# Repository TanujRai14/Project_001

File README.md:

# 🔌 Project_001: Smart USB Power Meter using ESP32, INA219 & OLED

This project is a compact **Smart USB Power Meter** designed using an **ESP32**, **INA219 current sensor**, and **OLED display**, all integrated on a custom **2-layer PCB**. The circuit allows real-time monitoring of **USB voltage and current** through a **Type-C connector**, displaying the results on a 0.96” OLED screen.

---

## ✨ Features

- ✅ Measures **voltage and current** of any USB-powered device
- 📟 Displays data on a **128x64 OLED** screen via **I2C**
- 📶 Powered by **ESP32** for wireless capabilities & efficient control
- 🔍 Uses **INA219** precision current sensor for accurate readings
- 🔧 Onboard **AMS1117** 5V to 3.3V regulator for safe ESP32 operation
- 🧵 Designed with **standard trace widths** (0.2mm, 0.3mm, 0.5mm)
- 🛠️ Full **GND pour** on bottom layer, all signals routed on top
- 📡 Dedicated **Antenna Keep-Out Zone** for WiFi stability

---

## 🧩 Hardware Components

| Component        | Description                                           |
|------------------|-------------------------------------------------------|
| **ESP32 Module** | WiFi-enabled microcontroller (ESP-WROOM-32)           |
| **INA219**       | I2C-based voltage and current sensor                  |
| **OLED Display** | 128x64 OLED via I2C (address: 0x3C or 0x78)           |
| **AMS1117-3.3V** | LDO regulator to step down 5V to 3.3V                  |
| **USB Type-C**   | Input connector for USB voltage/current measurement   |
| **Passives**     | Capacitors & resistors for filtering & pull-ups       |

---

## 🛠️ PCB Design Highlights

- 🔲 **2-layer PCB**
  - Top Layer: Signal routing
  - Bottom Layer: Solid GND plane for noise reduction

- 🔌 **Trace Widths**
  - Signal traces: `0.2 mm`
  - Power traces: `0.3 mm`
  - INA219 high-current path: `0.5 mm`

- 📏 **Routing Guidelines**
  - Uniform SPI/I2C trace lengths
  - Minimum crosstalk and EMI
  - Proper decoupling at power pins
  - Dedicated Keep-Out Zone for ESP32 Antenna

---

## ⚙️ Working Principle

1. A USB device is connected via the **USB Type-C** input (J1).
2. The **INA219 sensor** measures the input current and voltage.
3. **ESP32** reads the data from INA219 via **I2C protocol**.
4. The ESP32 processes the values and displays them on the **OLED**.
5. **AMS1117** provides regulated **3.3V** to ESP32 and peripherals.

---

## 🧠 ESP32 Pin Mapping

| ESP32 Pin | Connected To       | Function       |
|-----------|--------------------|----------------|
| GPIO 21   | SDA (INA219, OLED) | I2C Data (SDA) |
| GPIO 22   | SCL (INA219, OLED) | I2C Clock (SCL)|
| 3.3V      | VCC (All Modules)  | Power Supply   |
| GND       | GND Plane          | Common Ground  |

---

## 🔋 Power Supply

| Source     | Purpose                         |
|------------|----------------------------------|
| **5V Input** | USB Type-C (J1)                 |
| **3.3V Reg** | AMS1117 provides 3.3V to ESP32, INA219, OLED |

---

## 🖼 PCB Layout Summary

- 🧠 ESP32 placed at center with Antenna keep-out on the left
- 🔬 INA219 close to USB input for accurate shunt readings
- 🔌 AMS1117 and capacitors placed for clean 3.3V regulation
- 📟 OLED connector on top side for vertical screen mounting
- 📐 Optimized signal routing for analog/digital separation

---

## 📦 File Contents

- 📁 `Gerber Files` – Ready for PCB manufacturing
- 📁 `Schematic PDF` – Complete circuit diagram
- 📁 `Firmware Code` – ESP32 code to:
  - Read INA219 data
  - Update OLED display in real-time

---

## 🚀 Use Cases

- USB power monitor for embedded systems
- Current profiling for smartphones or peripherals
- Educational tool for learning power electronics and PCB design

---

## 💡 Future Improvements

- Add UART header for serial debugging/monitoring
- Add USB data passthrough or toggle switch
- Enable ESP32 WiFi mode for wireless logging and dashboard
- Add Li-ion charging support to make it portable

---

## 👨‍💻 Author

Designed  by **Tanuj Rai**

Feel free to fork and modify for your use. Pull requests are welcome!

---

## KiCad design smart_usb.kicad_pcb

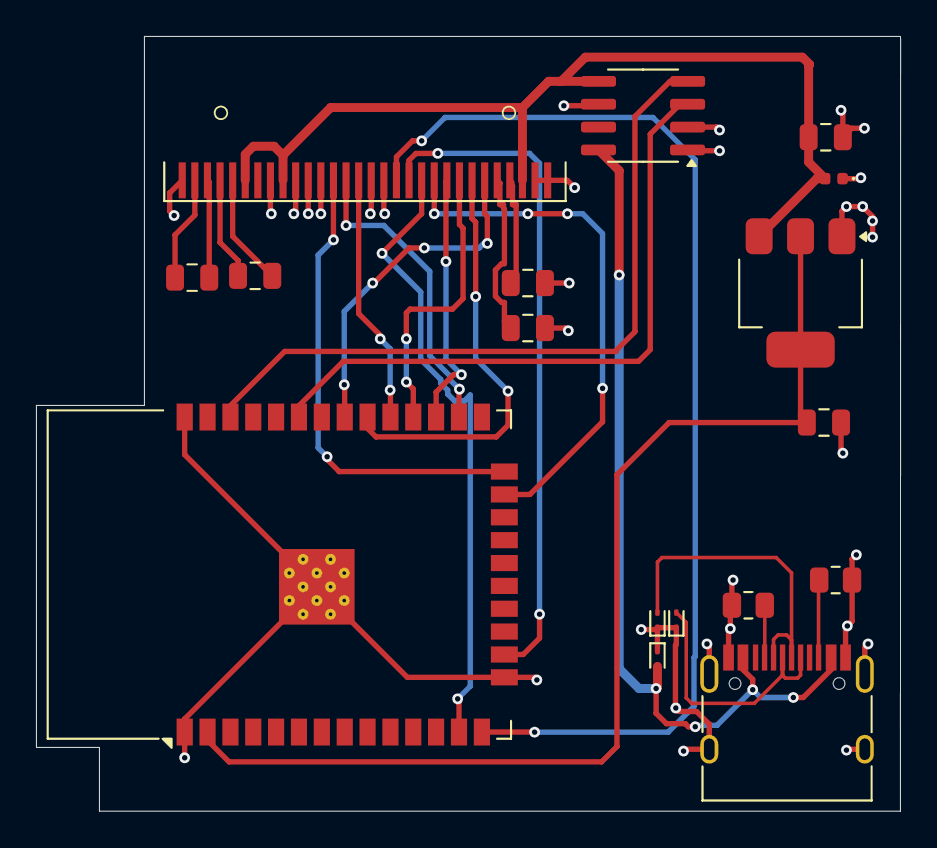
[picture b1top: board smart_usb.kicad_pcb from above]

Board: 2 copper layers, 48.0 x 43.0 mm, 17 parts (0 on the bottom side), 27 nets.

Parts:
C1: 10uF; C_0805_2012Metric
C2: 22uF; C_0805_2012Metric
C3, C4, C5: C; C_0805_2012Metric
D1: D_Schottky; D_0402_1005Metric
D2, D3, D4: ESD9B3.3ST5G; D_SOD-923
DS1: OLED-128O064D
J1: USB_C_Receptacle_USB2.0_16P; USB_C_Receptacle_HRO_TYPE-C-31-M-12
R1, R2: 5.1K; R_0805_2012Metric
R3: 910K; C_0805_2012Metric
U1: INA219AxD; SOIC-8_3.9x4.9mm_P1.27mm
U2: AMS1117; SOT-223-3_TabPin2
U3: ESP32-WROOM-32

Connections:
+3.3V: C2.1, U2.2 (VO), U3.2 (VDD)
+5V: C1.1, D1.2 (A), DS1.6 (VBAT), DS1.9 (VDD), DS1.28 (VCC), U1.5 (VS), U2.3 (VI)
GND: C1.2, C2.2, C5.2, D1.1 (K), D2.1 (A1), D3.1 (A1), D4.1 (A1), DS1.1 (GND), DS1.8 (VSS), DS1.10 (BS0), DS1.11 (BS1), DS1.12 (BS2), DS1.16 (R/~W), DS1.17 (E/~RD), DS1.29 (VLSS), DS1.30 (GND), J1.A1 (GND), J1.A12 (GND), J1.B1 (GND), J1.B12 (GND), J1.S1 (SHIELD), R1.2, R2.2, R3.2, U1.1 (A1), U1.2 (A0), U1.6 (GND), U2.1 (ADJ), U3.1 (GND), U3.15 (GND), U3.38 (GND), U3.39 (GND)
unnamed: D2.2 (A2), J1.A6 (D+), J1.B6 (D+)
unnamed: D3.2 (A2), J1.A7 (D-), J1.B7 (D-)
unnamed: C4.2, DS1.5 (C1N)
unnamed: C4.1, DS1.4 (C1P)
unnamed: C3.1, DS1.2 (C2N)
unnamed: C3.2, DS1.3 (C2P)
unnamed: DS1.18 (D0), U3.14 (IO12)
unnamed: DS1.19 (D1), U3.16 (IO13)
unnamed: DS1.20 (D2), U3.13 (IO14)
unnamed: DS1.21 (D3), U3.23 (IO15)
unnamed: DS1.22 (D4), U3.27 (IO16)
unnamed: DS1.23 (D5), U3.28 (IO17)
unnamed: DS1.24 (D6), U3.30 (IO18)
unnamed: DS1.25 (D7), U3.31 (IO19)
unnamed: DS1.15 (D/~C), U3.29 (IO5)
unnamed: DS1.26 (IREF), R3.1
unnamed: C5.1, DS1.27 (VCOMH)
unnamed: DS1.13 (~CS), U3.24 (IO2)
unnamed: DS1.14 (~RES), U3.26 (IO4)
unnamed: J1.A5 (CC1), R1.1
unnamed: J1.B5 (CC2), R2.1
SCL: U1.4 (SCL), U3.36 (IO22)
SDA: U1.3 (SDA), U3.33 (IO21)
VBUS: D4.2 (A2), J1.A4 (VBUS), J1.A9 (VBUS), J1.B4 (VBUS), J1.B9 (VBUS), U1.8 (IN+)

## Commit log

2025-07-27 README.md
2025-07-27 LICENSE
